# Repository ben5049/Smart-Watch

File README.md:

# Smart-Watch

## Introduction

This project aims to take a cheap, common smart watch and upgrade it by replacing the screen and all internal electronics with custom hardware.

## Repository structure

* [/Documentation](/Documentation/README.md) - all the documents to do with the project, including [hardware](/Documentation/Hardware.md) and [software](/Documentation/Software.md) design, datasheets, reference manuals, images etc.
* [/PCBs](/PCBs/README.md) - KiCad projects for all the circuit boards used, libraries for all components, and old versions.
* [/Firmware](/Firmware/README.md) - code for STM32 and nRF53 microcontrollers, including drivers for most chips.
* [/CAD](/CAD/README.md) - 3D models for components and assemblies, as well as 3D printing files.
* [/Simulations](/Simulations/README.md) - Spice simulations of certain (mainly analogue) circuits.

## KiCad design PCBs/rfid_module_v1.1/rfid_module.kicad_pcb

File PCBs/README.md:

# PCBs

## Core PCBs

* [Main board v3.1](/PCBs/watch_main_v3/) - display controller, power, wireless and most other features.
* [Lower flex v1.0](/PCBs/watch_lower/) - flexible PCB with heart rate sensor, power input and haptic motor.
* [Main board test rig v2.0](/PCBs/watch_test_rig_v2/) - pogo pin connectors for the main board, used for programming and debugging.
* [Main board test rig v2.0 support](/PCBs/watch_test_rig_support/) - adds mechanical support to the pogo pins of the main board test rig v2.

## Module PCBs
* [RFID module v1.1](/PCBs/rfid_module_v1.1/) - 125kHz RFID reciever and transmitter, based on the [Flipper Zero](https://docs.flipper.net/development/hardware/schematic/).
* [LoRa module](/PCBs/lora_module/) - LoRa reciever and transmitter using an STM32WL.
* [USB module](/PCBs/usb_module/) - Adds a USB-C port for charging and data.
* [Module test rig](/PCBs/module_test_rig/) - pogo pin connectors for modules, used for programming and debugging.

## Archived PCBs
* [Main board v1](/PCBs/archived/watch_main_v1/) - deprecated due to new screen with a different connector.
* [Main board v2](/PCBs/watch_main_v2/) - deprecated due to new wireless chip and minor errors that are listed [here](/Documentation/Future%20Changes.md).
* [Main board test rig v1](/PCBs/archived/watch_test_rig%20v1/) - deprecated with main board v1.
* [RFID module v1.0](/PCBs/archived/rfid_module_v1/) - deprecated due to inefficient routing (high layer count), and being the wrong dimensions.

## Library

[/component_library](/PCBs/component_library/) contains all the symbols, footprints, 3D models and drawings used in the PCBs. Projects all use relative paths to the library with ```../${KIPRMOD}/``` and as such are portable between devices as long as the folder structure is the same.

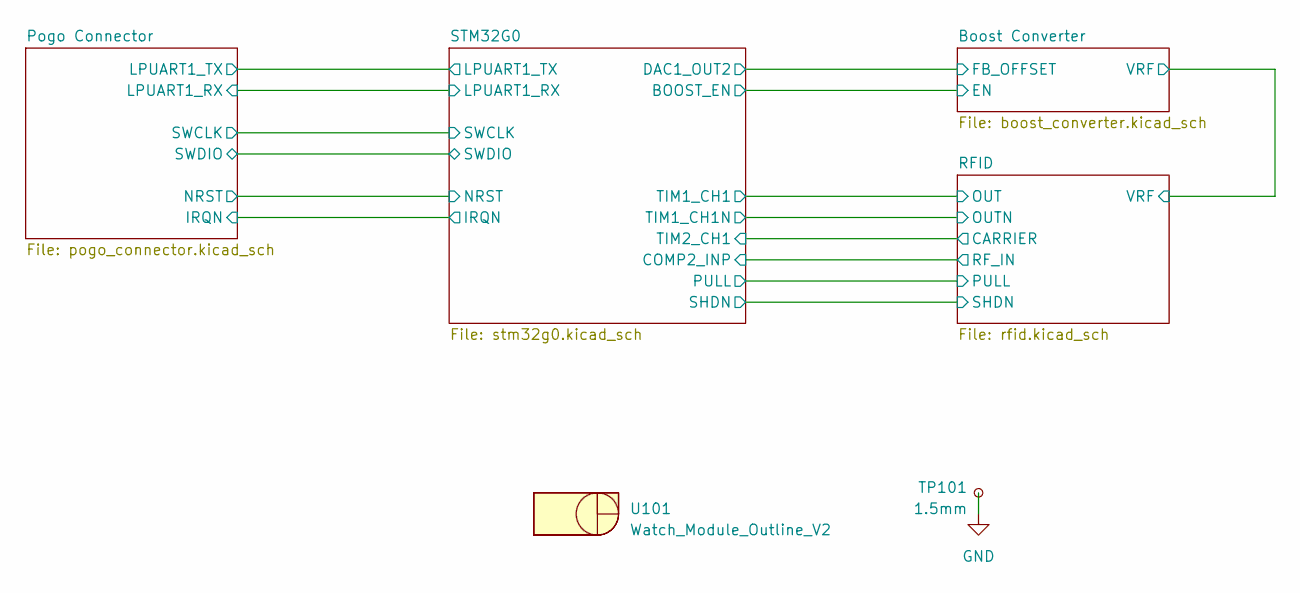
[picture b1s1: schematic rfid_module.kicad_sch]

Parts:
TP101: 1.5mm; TestPoint_Pad_D1.5mm
U101: Watch_Module_Outline_V2; Watch Module Outline V2

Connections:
GND: TP101.1; also elsewhere on the board

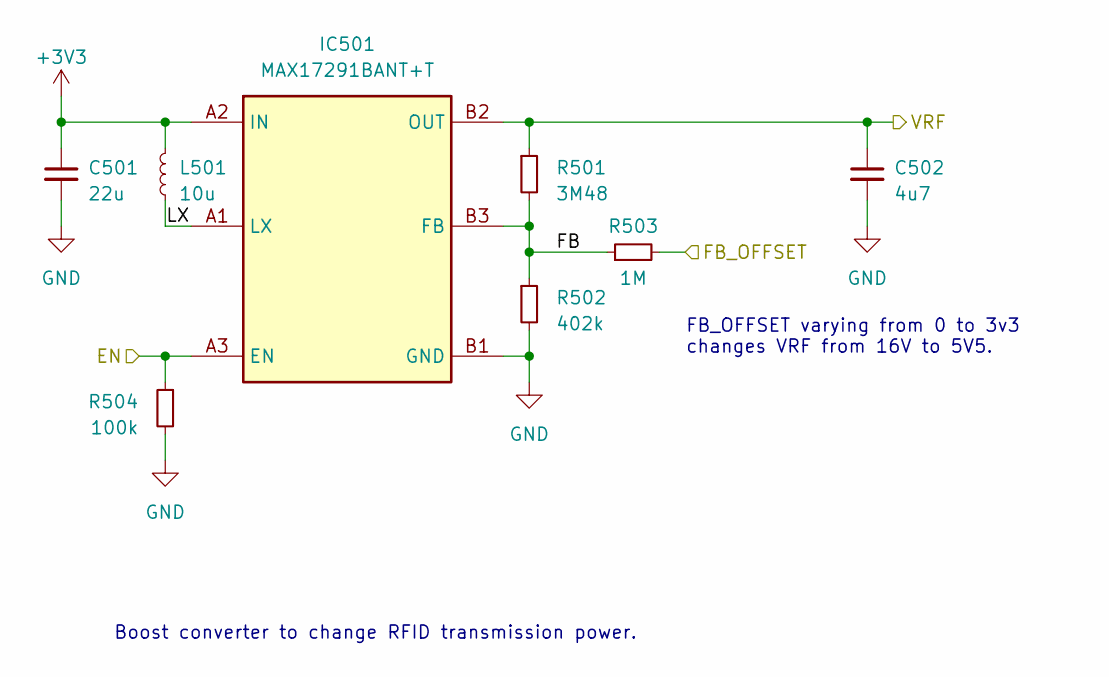
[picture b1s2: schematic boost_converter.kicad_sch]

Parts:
C501: 22u; C_0402_1005Metric
C502: 4u7; C_0402_1005Metric
IC501: MAX17291BANT+T; BGA6C40P3X2_127X87X50; Mouser Part Number 700-MAX17291BANT+T
L501: 10u; L_TDK_MLZ1608
R501: 3M48; R_0402_1005Metric
R502: 402k; R_0402_1005Metric
R503: 1M; R_0402_1005Metric
R504: 100k; R_0402_1005Metric

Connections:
+3V3: C501.1, IC501.A2 (IN), L501.1; also elsewhere on the board
/Boost Converter/EN: IC501.A3 (EN), R504.1; also elsewhere on the board
/Boost Converter/FB: IC501.B3 (FB), R501.2, R502.1, R503.1
/Boost Converter/FB_OFFSET: R503.2; also elsewhere on the board
/Boost Converter/LX: IC501.A1 (LX), L501.2
/Boost Converter/VRF: C502.1, IC501.B2 (OUT), R501.1; also elsewhere on the board
GND: C501.2, C502.2, IC501.B1 (GND), R502.2, R504.2; also elsewhere on the board

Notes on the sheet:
Boost converter to change RFID transmission power.
FB_OFFSET varying from 0 to 3v3 changes VRF from 16V to 5V5.

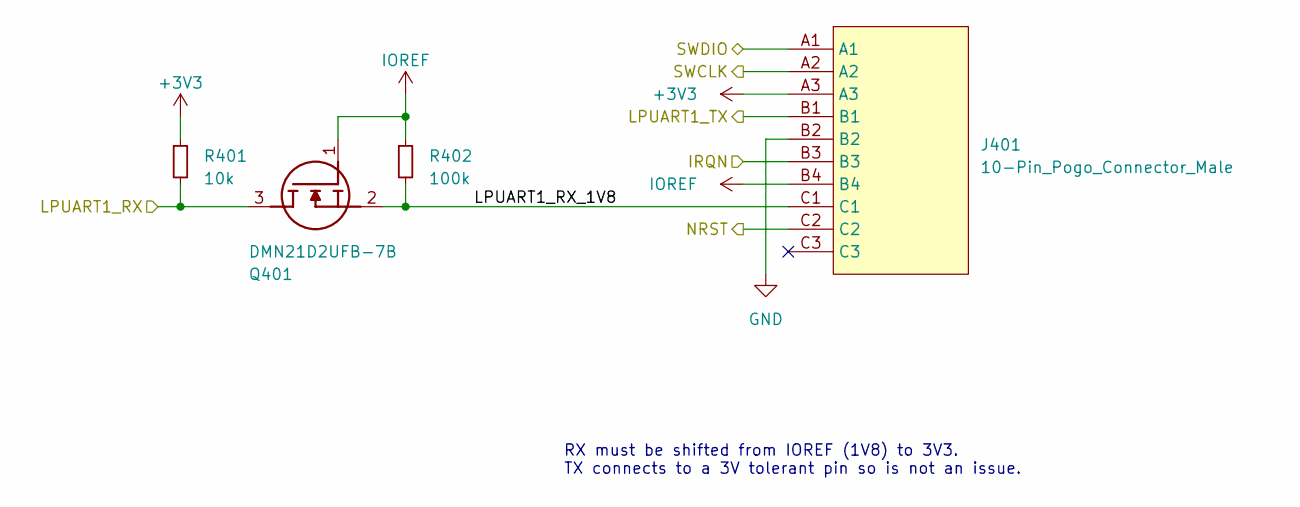
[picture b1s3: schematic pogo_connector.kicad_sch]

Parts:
J401: 10-Pin_Pogo_Connector_Male; 10-Pin Pogo Connector Male
Q401: DMN21D2UFB-7B; DMN21D2UFB7B; Mouser Part Number 621-DMN21D2UFB-7B
R401: 10k; R_0402_1005Metric
R402: 100k; R_0402_1005Metric

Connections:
+3V3: J401.A3, R401.1; also elsewhere on the board
/Pogo Connector/IRQN: J401.B3; also elsewhere on the board
/Pogo Connector/LPUART1_RX: Q401.3 (D), R401.2; also elsewhere on the board
/Pogo Connector/LPUART1_RX_1V8: J401.C1, Q401.2 (S), R402.2
/Pogo Connector/LPUART1_TX: J401.B1; also elsewhere on the board
/Pogo Connector/NRST: J401.C2; also elsewhere on the board
/Pogo Connector/SWCLK: J401.A2; also elsewhere on the board
/Pogo Connector/SWDIO: J401.A1; also elsewhere on the board
GND: J401.B2; also elsewhere on the board
IOREF: J401.B4, Q401.1 (G), R402.1

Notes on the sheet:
RX must be shifted from IOREF (1V8) to 3V3. TX connects to a 3V tolerant pin so is not an issue.

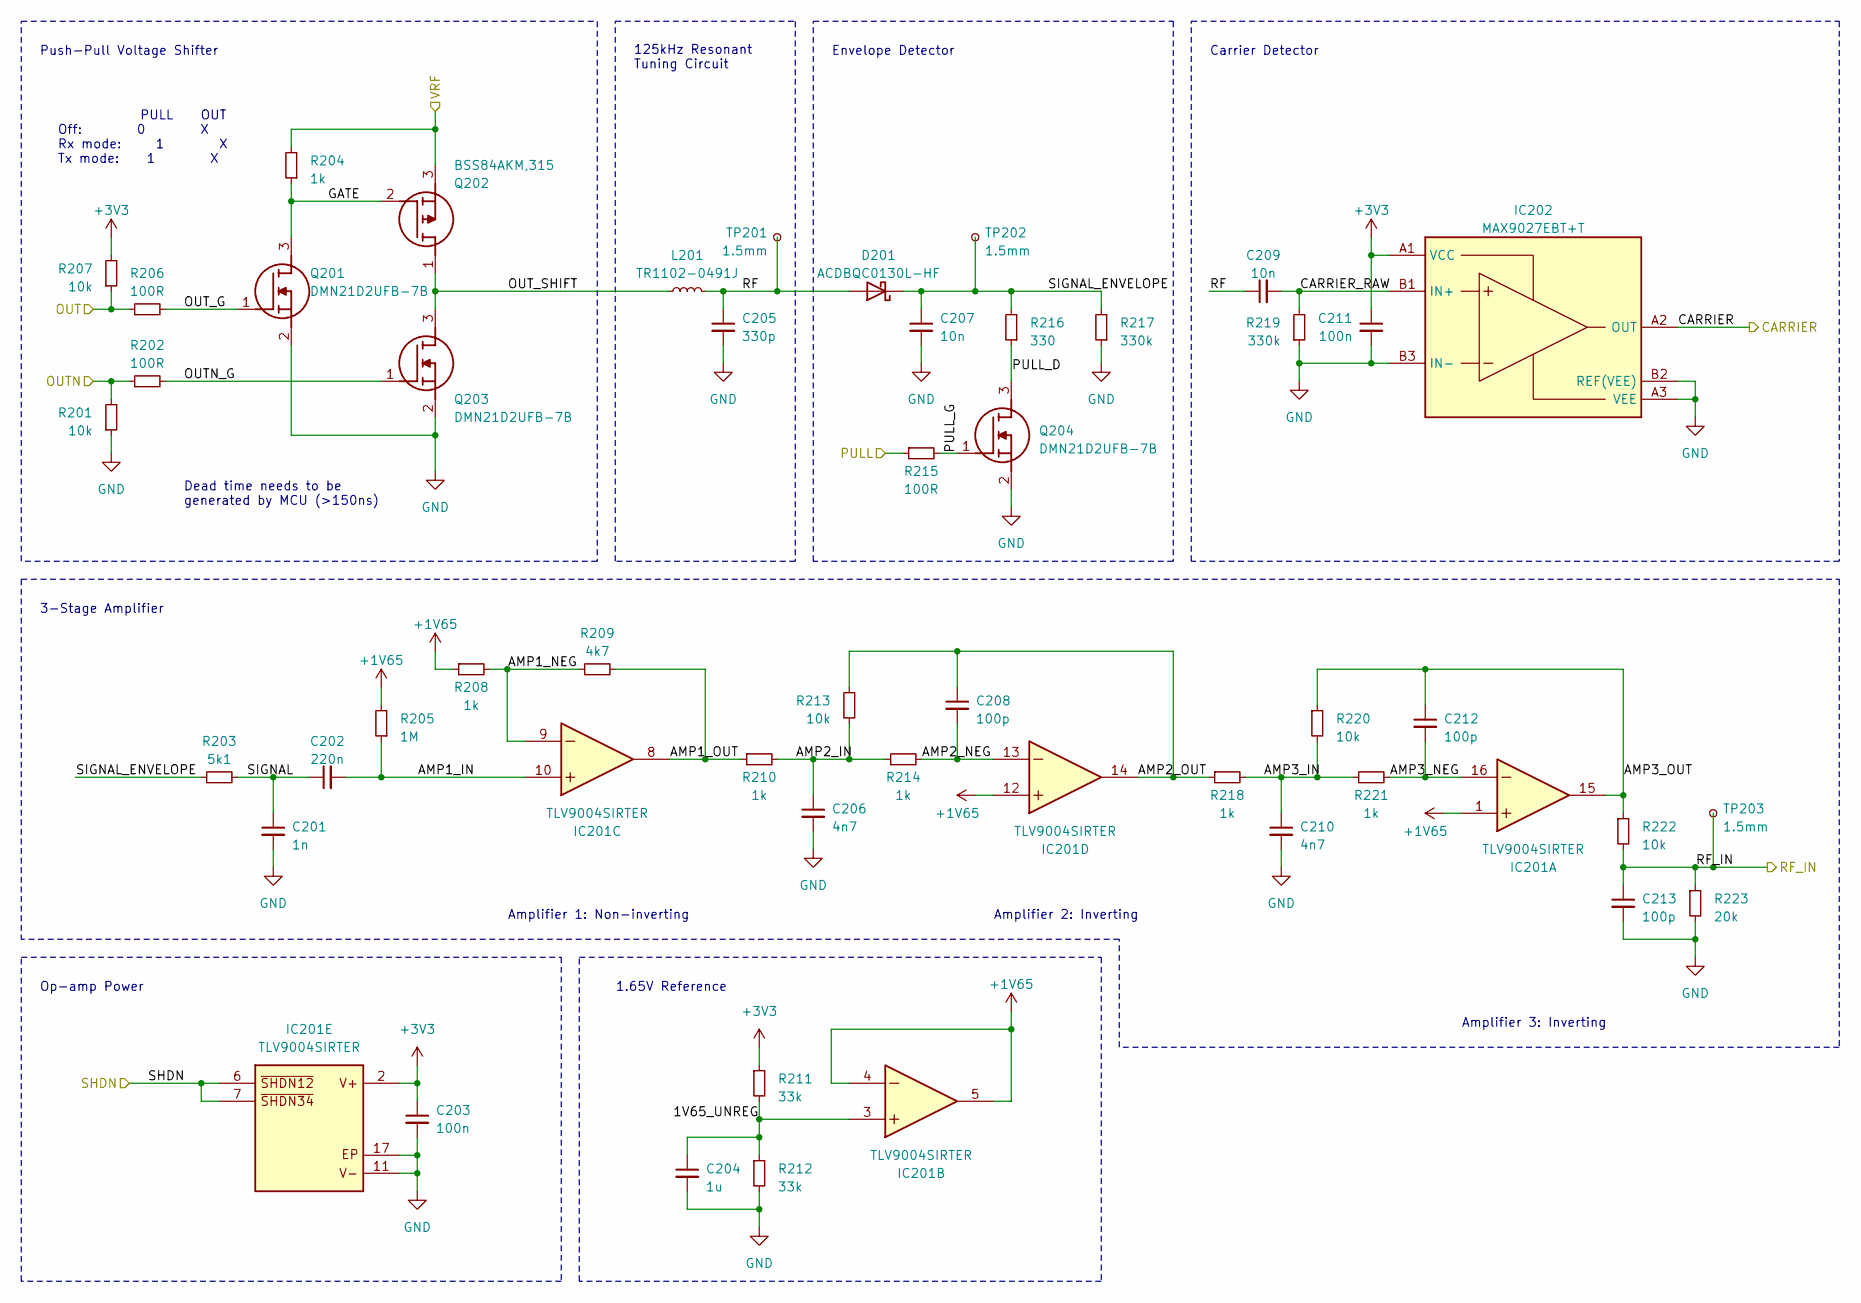
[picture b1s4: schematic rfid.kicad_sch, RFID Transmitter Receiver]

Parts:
C201: 1n; C_0402_1005Metric
C202: 220n; C_0402_1005Metric
C203, C211: 100n; C_0402_1005Metric
C204: 1u; C_0402_1005Metric
C205: 330p; C_0402_1005Metric
C206, C210: 4n7; C_0402_1005Metric
C207, C209: 10n; C_0402_1005Metric
C208, C212, C213: 100p; C_0402_1005Metric
D201: ACDBQC0130L-HF; D_SOD-923
IC201: TLV9004SIRTER; QFN50P300X300X80-17N-D; Mouser Part Number 595-TLV9004SIRTER
IC202: MAX9027EBT+T; BGA6C50P3X2_152X100X69; Mouser Part Number 700-MAX9028EBTT
L201: TR1102-0491J
Q201, Q203, Q204: DMN21D2UFB-7B; DMN21D2UFB7B; Mouser Part Number 621-DMN21D2UFB-7B
Q202: BSS84AKM,315; DMP21D5UFB47B; Mouser Part Number 771-BSS84AKM315
R201, R207, R213, R220, R222: 10k; R_0402_1005Metric
R202, R206, R215: 100R; R_0402_1005Metric
R203: 5k1; R_0402_1005Metric
R204, R208, R210, R214, R218, R221: 1k; R_0402_1005Metric
R205: 1M; R_0402_1005Metric
R209: 4k7; R_0402_1005Metric
R211, R212: 33k; R_0402_1005Metric
R216: 330; R_0402_1005Metric
R217, R219: 330k; R_0402_1005Metric
R223: 20k; R_0402_1005Metric
TP201, TP202, TP203: 1.5mm; TestPoint_Pad_D1.5mm

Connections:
+1V65: IC201.1 (IN1+), IC201.4 (IN2-), IC201.5 (OUT2), IC201.12 (IN4+), R205.2, R208.1
+3V3: C203.1, C211.1, IC201.2 (V+), IC202.A1 (VCC), R207.2, R211.1; also elsewhere on the board
/Boost Converter/VRF: Q202.3 (S), R204.2; also elsewhere on the board
/RFID/1V65_UNREG: C204.1, IC201.3 (IN2+), R211.2, R212.1
/RFID/AMP1_IN: C202.2, IC201.10 (IN3+), R205.1
/RFID/AMP1_NEG: IC201.9 (IN3-), R208.2, R209.1
/RFID/AMP1_OUT: IC201.8 (OUT3), R209.2, R210.1
/RFID/AMP2_IN: C206.1, R210.2, R213.2, R214.1
/RFID/AMP2_NEG: C208.2, IC201.13 (IN4-), R214.2
/RFID/AMP2_OUT: C208.1, IC201.14 (OUT4), R213.1, R218.1
/RFID/AMP3_IN: C210.1, R218.2, R220.2, R221.1
/RFID/AMP3_NEG: C212.2, IC201.16 (IN1-), R221.2
/RFID/AMP3_OUT: C212.1, IC201.15 (OUT1), R220.1, R222.1
/RFID/CARRIER: IC202.A2 (OUT); also elsewhere on the board
/RFID/CARRIER_RAW: C209.2, IC202.B1 (IN+), R219.2
/RFID/GATE: Q201.3 (D), Q202.2 (G), R204.1
/RFID/OUT: R206.1, R207.1; also elsewhere on the board
/RFID/OUTN: R201.2, R202.1; also elsewhere on the board
/RFID/OUTN_G: Q203.1 (G), R202.2
/RFID/OUT_G: Q201.1 (G), R206.2
/RFID/OUT_SHIFT: L201.1, Q202.1 (D), Q203.3 (D)
/RFID/PULL: R215.1; also elsewhere on the board
/RFID/PULL_D: Q204.3 (D), R216.1
/RFID/PULL_G: Q204.1 (G), R215.2
/RFID/RF: C205.1, C209.1, D201.2 (A), L201.2, TP201.1
/RFID/RF_IN: C213.1, R222.2, R223.1, TP203.1; also elsewhere on the board
/RFID/SHDN: IC201.6 (~SHDN12), IC201.7 (~SHDN34); also elsewhere on the board
/RFID/SIGNAL: C201.1, C202.1, R203.2
/RFID/SIGNAL_ENVELOPE: C207.1, D201.1 (K), R203.1, R216.2, R217.2, TP202.1
GND: C201.2, C203.2, C204.2, C205.2, C206.2, C207.2, C210.2, C211.2, C213.2, IC201.11 (V-), IC201.17 (EP), IC202.A3 (VEE), IC202.B2 (REF(VEE)), IC202.B3 (IN-), Q201.2 (S), Q203.2 (S), Q204.2 (S), R201.1, R212.2, R217.1, R219.1, R223.2; also elsewhere on the board

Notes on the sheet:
Amplifier 3: Inverting
Carrier Detector
Op-amp Power
Push-Pull Voltage Shifter
3-Stage Amplifier
Amplifier 1: Non-inverting
125kHz Resonant Tuning Circuit
Envelope Detector
Amplifier 2: Inverting
PULL OUT Off: 0 X Rx mode: 1 X Tx mode: 1 X
Dead time needs to be generated by MCU (>150ns)
1.65V Reference

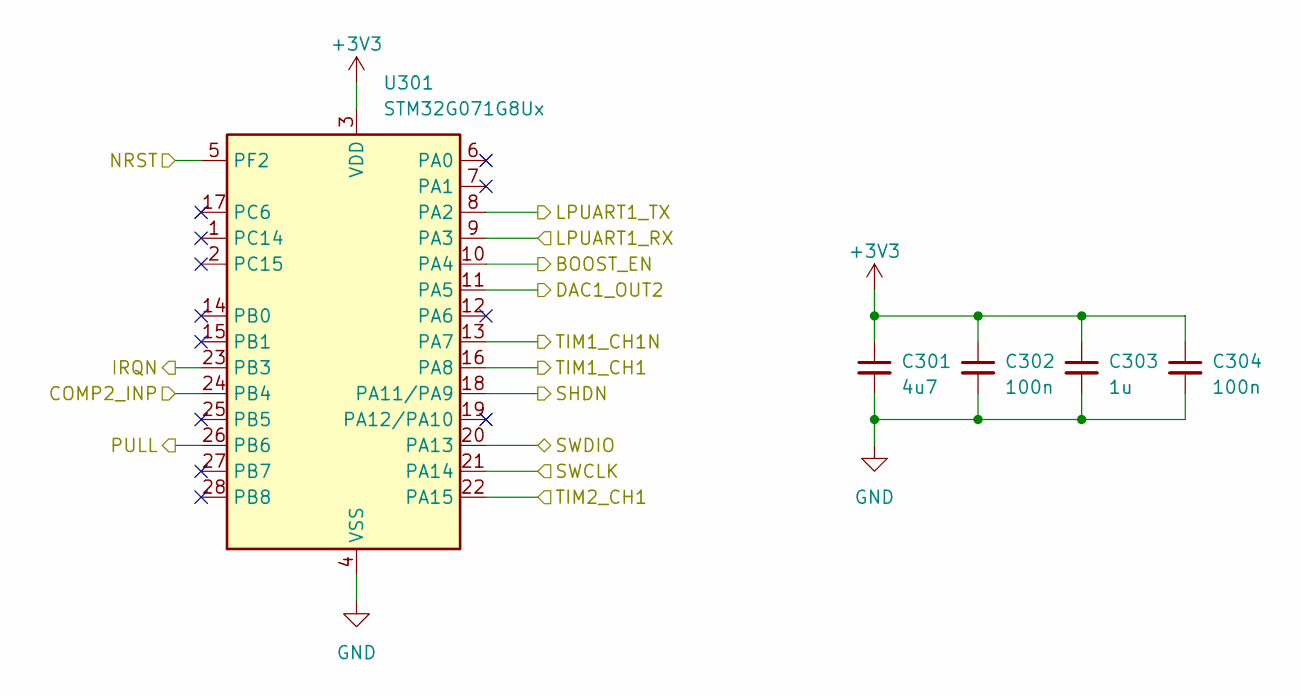
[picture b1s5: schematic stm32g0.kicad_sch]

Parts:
C301: 4u7; C_0402_1005Metric
C302, C304: 100n; C_0402_1005Metric
C303: 1u; C_0402_1005Metric
U301: STM32G071G8Ux; QFN-28_4x4mm_P0.5mm

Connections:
+3V3: C301.1, C302.1, C303.1, C304.1, U301.3 (VDD); also elsewhere on the board
/Boost Converter/EN: U301.10 (PA4); also elsewhere on the board
/Boost Converter/FB_OFFSET: U301.11 (PA5); also elsewhere on the board
/Pogo Connector/IRQN: U301.23 (PB3); also elsewhere on the board
/Pogo Connector/LPUART1_RX: U301.9 (PA3); also elsewhere on the board
/Pogo Connector/LPUART1_TX: U301.8 (PA2); also elsewhere on the board
/Pogo Connector/NRST: U301.5 (PF2); also elsewhere on the board
/Pogo Connector/SWCLK: U301.21 (PA14); also elsewhere on the board
/Pogo Connector/SWDIO: U301.20 (PA13); also elsewhere on the board
/RFID/CARRIER: U301.22 (PA15); also elsewhere on the board
/RFID/OUT: U301.16 (PA8); also elsewhere on the board
/RFID/OUTN: U301.13 (PA7); also elsewhere on the board
/RFID/PULL: U301.26 (PB6); also elsewhere on the board
/RFID/RF_IN: U301.24 (PB4); also elsewhere on the board
/RFID/SHDN: U301.18 (PA11/PA9); also elsewhere on the board
GND: C301.2, C302.2, C303.2, C304.2, U301.4 (VSS); also elsewhere on the board

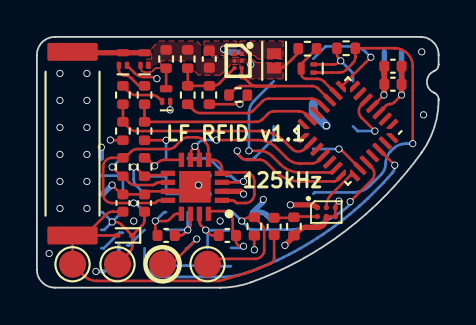
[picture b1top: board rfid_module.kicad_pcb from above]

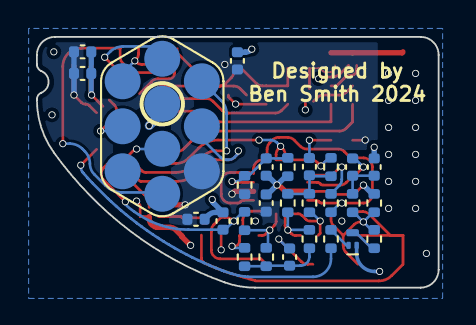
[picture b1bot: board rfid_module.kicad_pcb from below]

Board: 4 copper layers, 22.3 x 13.9 mm, 66 parts (27 on the bottom side), 42 nets.

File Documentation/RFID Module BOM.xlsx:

ICs
 |  | TLV9004SIRTER |  | 1 | 0.61 | Quad op amp |  | https://www.mouser.co.uk/ProductDetail/Texas-Instruments/TLV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
 |  | MAX9027EBT+T |  | 1 | 1.26 | Comparator |  | https://www.mouser.co.uk/ProductDetail/Analog-Devices-Maxim-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
Discrete Semis | FETs | DMN21D2UFB-7B |  | 3 | 0.28999999999999998 | RFID NMOS |  | https://www.mouser.co.uk/ProductDetail/Diodes-Incorporated/D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
 |  | DMP21D5UFB4-7B |  | 1 | 0.3 | RFID PMOS |  | https://www.mouser.co.uk/ProductDetail/Diodes-Incorporated/D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
 | Diodes | ACDBQC0130L-HF |  | 1 | 0.27 | RFID Envelope detector diode |  | https://www.mouser.co.uk/ProductDetail/Comchip-Technology/AC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
Passives | Inductors | TR1102-0491J | 4.91mH | 1 | 5 | RFID z-axis transponder coil | y | https://www.grupopremo.com/en/tr1102-xy-axis-smd-ferrite-rfi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

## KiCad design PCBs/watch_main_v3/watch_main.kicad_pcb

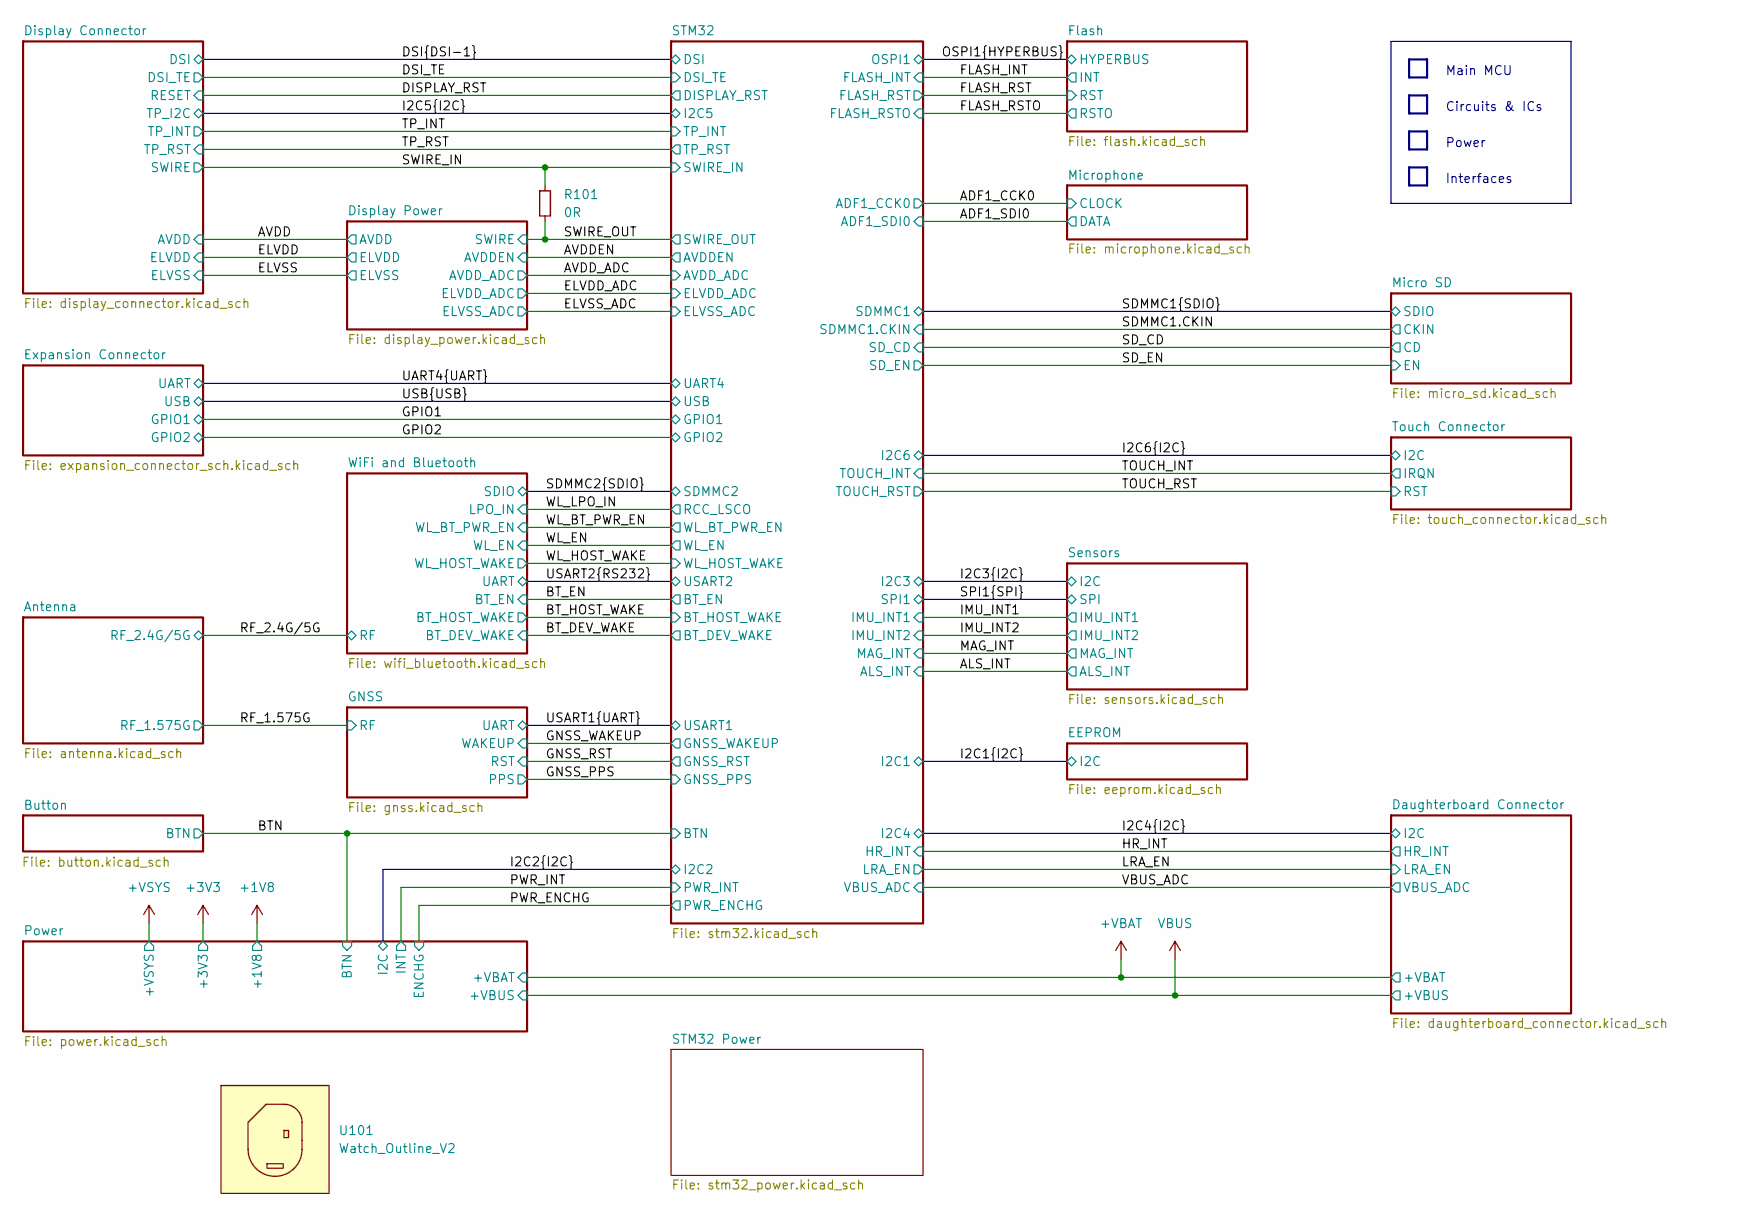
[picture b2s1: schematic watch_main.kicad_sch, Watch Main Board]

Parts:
R101: 0R; R_0402_1005Metric
U101: Watch_Outline_V2; Watch Outline V3

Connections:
/SWIRE_IN: R101.1; also elsewhere on the board
/SWIRE_OUT: R101.2; also elsewhere on the board

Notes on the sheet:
Interfaces
Circuits & ICs
Power
Main MCU

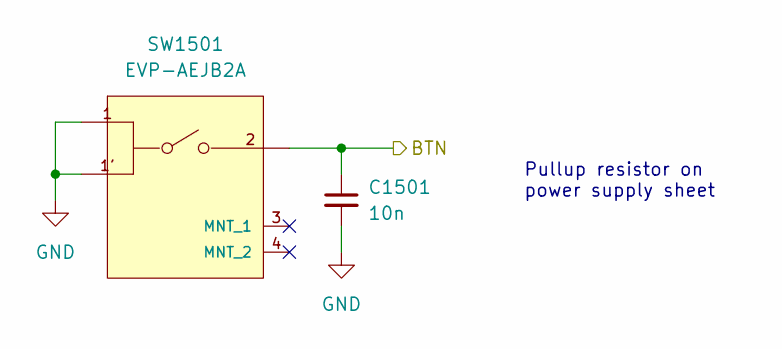
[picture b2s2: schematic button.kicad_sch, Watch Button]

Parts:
C1501: 10n; C_0402_1005Metric
SW1501: EVP-AEJB2A; Panasonic-EVP-AEJB2A-MFG; voltage rating DC 15V; mouser part number 667-EVP-AEJB2A; digikey description SWITCH TACTILE SPST-NO 0.02A 15V

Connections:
/BTN: C1501.1, SW1501.2; also elsewhere on the board
GND: C1501.2, SW1501.1, SW1501.1'; also elsewhere on the board

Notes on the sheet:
Pullup resistor on power supply sheet

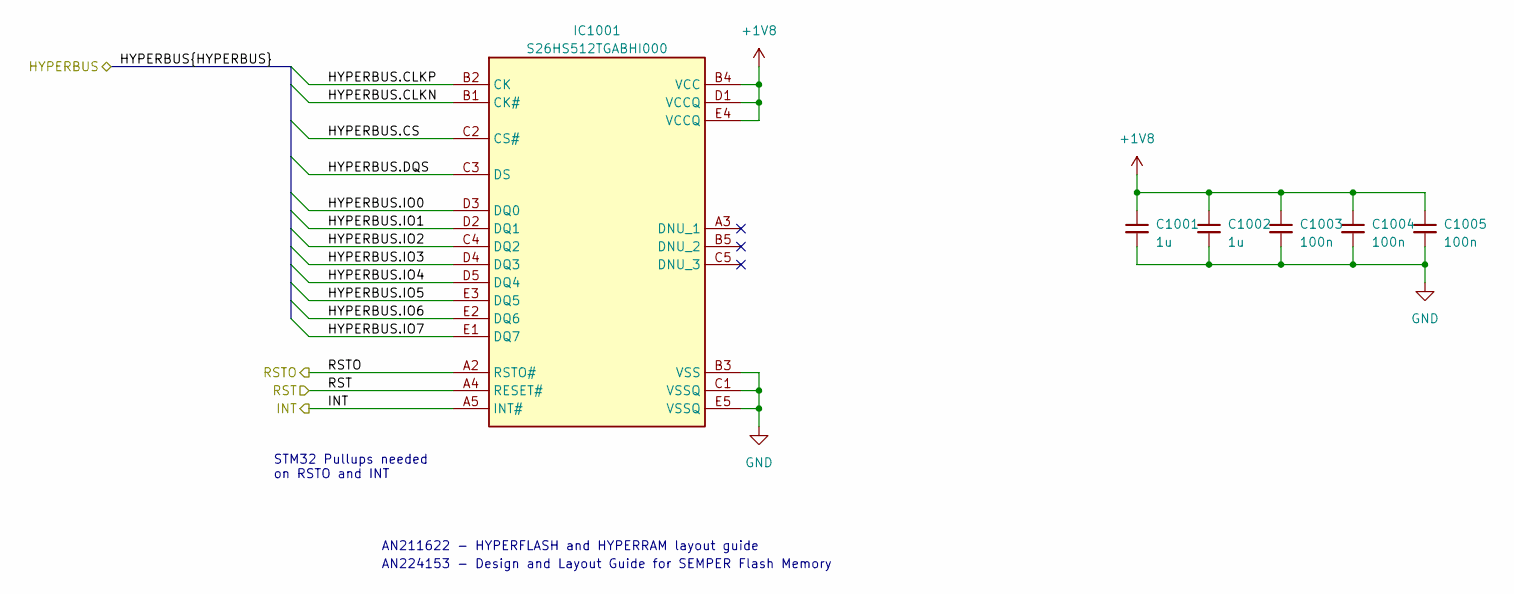
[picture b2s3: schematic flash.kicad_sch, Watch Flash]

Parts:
C1001, C1002: 1u; C_0402_1005Metric
C1003, C1004, C1005: 100n; C_0402_1005Metric
IC1001: S26HS512TGABHI000; BGA24C100P5X5_600X800X100; Mouser Part Number 727-S26HS512TGABHI00

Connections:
+1V8: C1001.1, C1002.1, C1003.1, C1004.1, C1005.1, IC1001.B4 (VCC), IC1001.D1 (VCCQ), IC1001.E4 (VCCQ); also elsewhere on the board
/FLASH_INT: IC1001.A5 (INT#); also elsewhere on the board
/FLASH_RST: IC1001.A4 (RESET#); also elsewhere on the board
/FLASH_RSTO: IC1001.A2 (RSTO#); also elsewhere on the board
/OSPI1.CLKN: IC1001.B1 (CK#); also elsewhere on the board
/OSPI1.CLKP: IC1001.B2 (CK); also elsewhere on the board
/OSPI1.CS: IC1001.C2 (CS#); also elsewhere on the board
/OSPI1.DQS: IC1001.C3 (DS); also elsewhere on the board
/OSPI1.IO0: IC1001.D3 (DQ0); also elsewhere on the board
/OSPI1.IO1: IC1001.D2 (DQ1); also elsewhere on the board
/OSPI1.IO2: IC1001.C4 (DQ2); also elsewhere on the board
/OSPI1.IO3: IC1001.D4 (DQ3); also elsewhere on the board
/OSPI1.IO4: IC1001.D5 (DQ4); also elsewhere on the board
/OSPI1.IO5: IC1001.E3 (DQ5); also elsewhere on the board
/OSPI1.IO6: IC1001.E2 (DQ6); also elsewhere on the board
/OSPI1.IO7: IC1001.E1 (DQ7); also elsewhere on the board
GND: C1001.2, C1002.2, C1003.2, C1004.2, C1005.2, IC1001.B3 (VSS), IC1001.C1 (VSSQ), IC1001.E5 (VSSQ); also elsewhere on the board

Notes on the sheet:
STM32 Pullups needed on RSTO and INT
AN224153 - Design and Layout Guide for SEMPER Flash Memory
AN211622 - HYPERFLASH and HYPERRAM layout guide

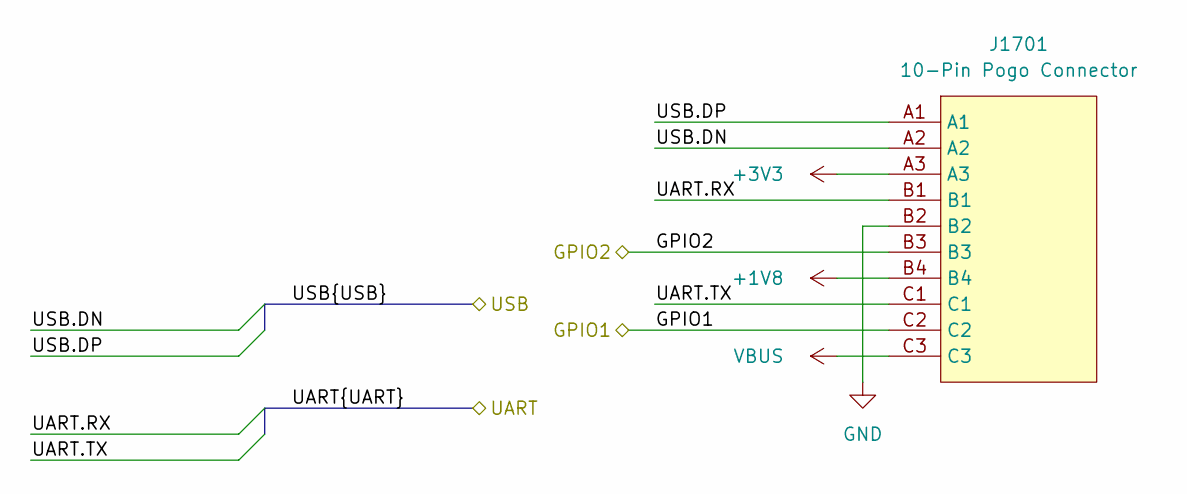
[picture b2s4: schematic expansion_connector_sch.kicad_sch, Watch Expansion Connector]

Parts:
J1701: 10-Pin Pogo Connector

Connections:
+1V8: J1701.B4; also elsewhere on the board
+3V3: J1701.A3; also elsewhere on the board
/GPIO1: J1701.C2; also elsewhere on the board
/GPIO2: J1701.B3; also elsewhere on the board
/UART4.RX: J1701.B1; also elsewhere on the board
/UART4.TX: J1701.C1; also elsewhere on the board
/USB.DN: J1701.A2; also elsewhere on the board
/USB.DP: J1701.A1; also elsewhere on the board
GND: J1701.B2; also elsewhere on the board
VBUS: J1701.C3; also elsewhere on the board

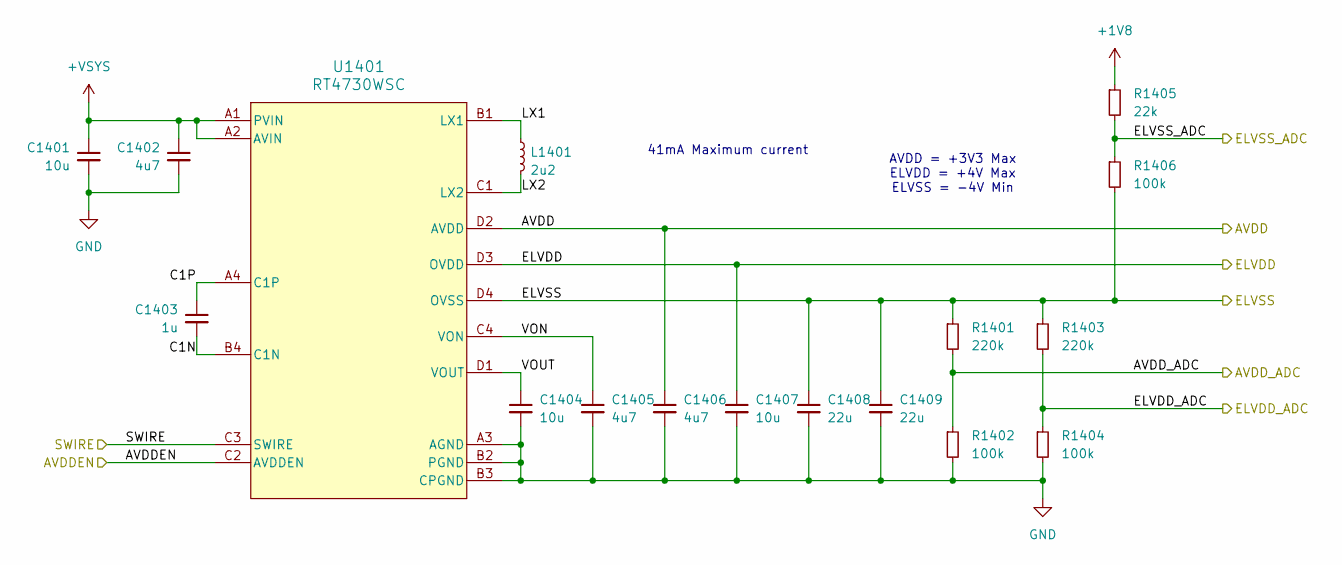
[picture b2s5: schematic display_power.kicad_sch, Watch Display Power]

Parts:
C1401, C1404, C1407: 10u; C_0402_1005Metric
C1402, C1405, C1406: 4u7; C_0402_1005Metric
C1403: 1u; C_0402_1005Metric
C1408, C1409: 22u; C_0402_1005Metric
L1401: 2u2; L_Murata_DFE201610P
R1401, R1403: 220k; R_0402_1005Metric
R1402, R1404, R1406: 100k; R_0402_1005Metric
R1405: 22k; R_0402_1005Metric
U1401: RT4730WSC

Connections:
+1V8: R1405.1; also elsewhere on the board
+VSYS: C1401.1, C1402.1, U1401.A1 (PVIN), U1401.A2 (AVIN); also elsewhere on the board
/AVDD: C1406.1, U1401.D2 (AVDD); also elsewhere on the board
/AVDDEN: U1401.C2 (AVDDEN); also elsewhere on the board
/AVDD_ADC: R1401.2, R1402.1; also elsewhere on the board
/Display Power/C1N: C1403.2, U1401.B4 (C1N)
/Display Power/C1P: C1403.1, U1401.A4 (C1P)
/Display Power/LX1: L1401.1, U1401.B1 (LX1)
/Display Power/LX2: L1401.2, U1401.C1 (LX2)
/Display Power/VON: C1405.1, U1401.C4 (VON)
/Display Power/VOUT: C1404.1, U1401.D1 (VOUT)
/ELVDD: C1407.1, U1401.D3 (OVDD); also elsewhere on the board
/ELVDD_ADC: R1403.2, R1404.1; also elsewhere on the board
/ELVSS: C1408.1, C1409.1, R1401.1, R1403.1, R1406.2, U1401.D4 (OVSS); also elsewhere on the board
/ELVSS_ADC: R1405.2, R1406.1; also elsewhere on the board
/SWIRE_OUT: U1401.C3 (SWIRE); also elsewhere on the board
GND: C1401.2, C1402.2, C1404.2, C1405.2, C1406.2, C1407.2, C1408.2, C1409.2, R1402.2, R1404.2, U1401.A3 (AGND), U1401.B2 (PGND), U1401.B3 (CPGND); also elsewhere on the board

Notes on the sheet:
AVDD = +3V3 Max ELVDD = +4V Max ELVSS = -4V Min
41mA Maximum current

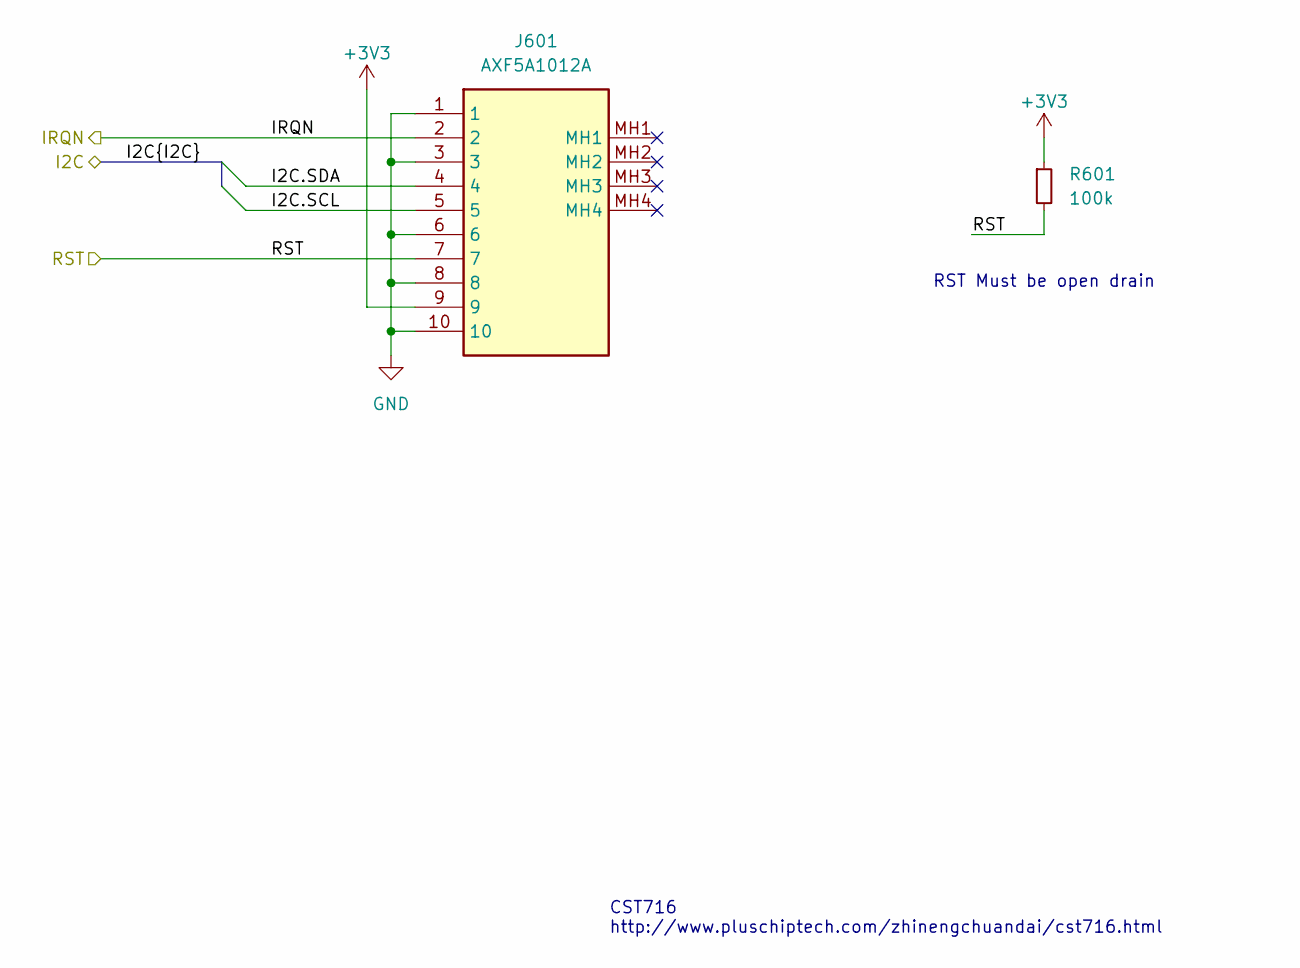
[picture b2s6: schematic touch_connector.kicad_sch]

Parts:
J601: AXF5A1012A
R601: 100k; R_0402_1005Metric

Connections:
+3V3: J601.9, R601.1; also elsewhere on the board
/I2C6.SCL: J601.5; also elsewhere on the board
/I2C6.SDA: J601.4; also elsewhere on the board
/TOUCH_INT: J601.2; also elsewhere on the board
/TOUCH_RST: J601.7, R601.2; also elsewhere on the board
GND: J601.1, J601.3, J601.6, J601.8, J601.10; also elsewhere on the board

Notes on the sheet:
RST Must be open drain
CST716 http://www.pluschiptech.com/zhinengchuandai/cst716.html

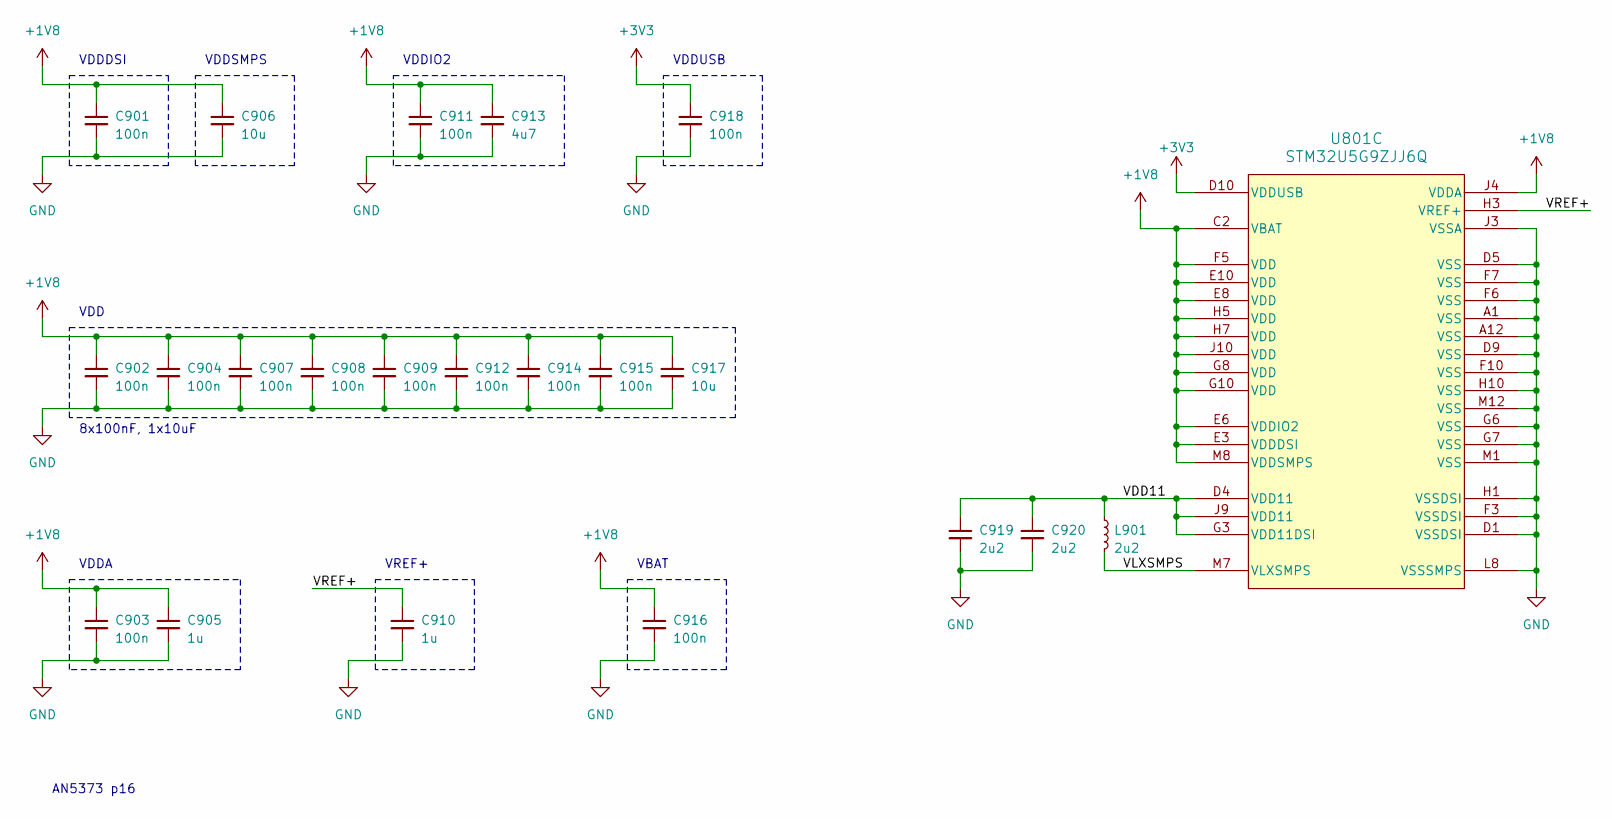
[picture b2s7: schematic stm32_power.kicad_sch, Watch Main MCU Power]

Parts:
C901, C902, C903, C904, C907, C908, C909, C911, C912, C914, C915, C916, C918: 100n; C_0201_0603Metric
C905, C910: 1u; C_0201_0603Metric
C906, C917: 10u; C_0402_1005Metric
C913: 4u7; C_0402_1005Metric
C919, C920: 2u2; C_0201_0603Metric
L901: 2u2; L_Murata_DFE201610P
U801: STM32U5G9ZJJ6Q; UFBGA144_STM

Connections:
+1V8: C901.1, C902.1, C903.1, C904.1, C905.1, C906.1, C907.1, C908.1, C909.1, C911.1, C912.1, C913.1, C914.1, C915.1, C916.1, C917.1, U801.C2 (VBAT), U801.E3 (VDDDSI), U801.E6 (VDDIO2), U801.E8 (VDD), U801.E10 (VDD), U801.F5 (VDD), U801.G8 (VDD), U801.G10 (VDD), U801.H5 (VDD), U801.H7 (VDD), U801.J4 (VDDA), U801.J10 (VDD), U801.M8 (VDDSMPS); also elsewhere on the board
+3V3: C918.1, U801.D10 (VDDUSB); also elsewhere on the board
/STM32 Power/VDD11: C919.1, C920.1, L901.1, U801.D4 (VDD11), U801.G3 (VDD11DSI), U801.J9 (VDD11)
/STM32 Power/VLXSMPS: L901.2, U801.M7 (VLXSMPS)
/STM32 Power/VREF+: C910.1, U801.H3 (VREF+)
GND: C901.2, C902.2, C903.2, C904.2, C905.2, C906.2, C907.2, C908.2, C909.2, C910.2, C911.2, C912.2, C913.2, C914.2, C915.2, C916.2, C917.2, C918.2, C919.2, C920.2, U801.A1 (VSS), U801.A12 (VSS), U801.D1 (VSSDSI), U801.D5 (VSS), U801.D9 (VSS), U801.F3 (VSSDSI), U801.F6 (VSS), U801.F7 (VSS), U801.F10 (VSS), U801.G6 (VSS), U801.G7 (VSS), U801.H1 (VSSDSI), U801.H10 (VSS), U801.J3 (VSSA), U801.L8 (VSSSMPS), U801.M1 (VSS), U801.M12 (VSS); also elsewhere on the board

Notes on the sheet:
VDDUSB
VDDIO2
VREF+
VDD
VDDSMPS
VDDA
VBAT
AN5373 p16
8x100nF, 1x10uF
VDDDSI
